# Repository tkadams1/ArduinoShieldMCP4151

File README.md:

# ArduinoShieldMCP4151
Code for driving the Arduino shield including a python serial monitor program, ROS2 subscriber code, and the necessary code to Drive the arduino.  Also include is the custom arduino shield KiCad files to create the shield itself.

Component List:
  - MCP 4151 digital potentiometer
  - JZC-11F relay
  - 5k ohms THT resistor
  - Arduino header pins
  - 2.54 mm 2 socket screw terminals

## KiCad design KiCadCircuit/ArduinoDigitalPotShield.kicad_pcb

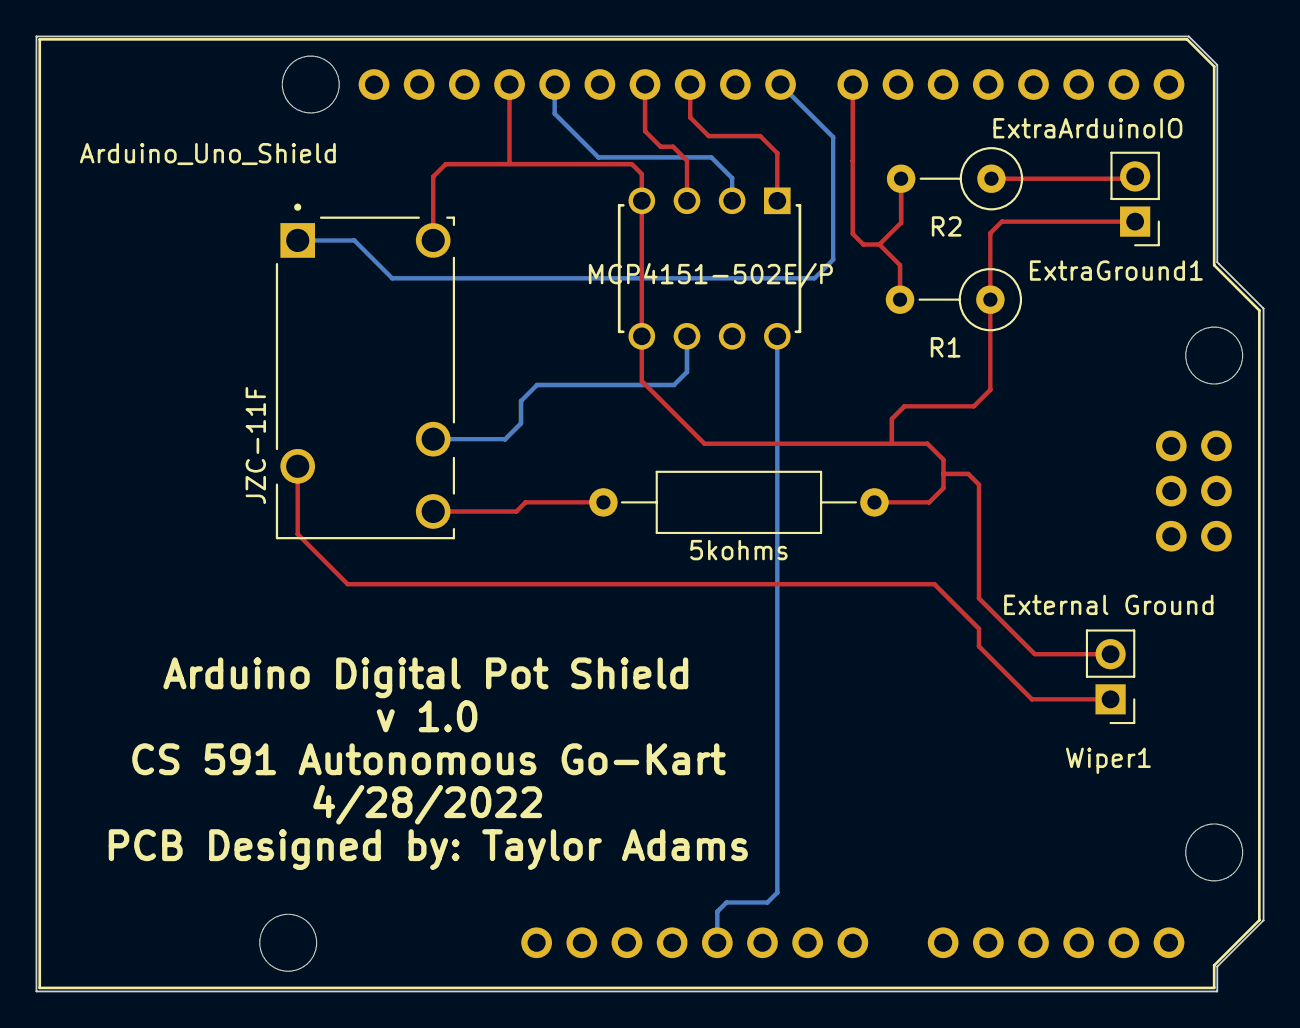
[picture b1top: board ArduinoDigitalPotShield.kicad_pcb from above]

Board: 2 copper layers, 69.0 x 53.7 mm, 8 parts (0 on the bottom side), 11 nets.

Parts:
5kohms: R; R_Axial_DIN0309_L9.0mm_D3.2mm_P15.24mm_Horizontal
ExtraGround1: ExtraArduinoIO; PinHeader_1x02_P2.54mm_Vertical
K1: JZC-11F; RELAY_J0971CS5VDC.45
R1, R2: R; R_Axial_DIN0309_L9.0mm_D3.2mm_P5.08mm_Vertical
U2: MCP4151-502E/P; DIP254P762X533-8
Wiper1: External Ground; PinHeader_1x02_P2.54mm_Vertical
XA1: Arduino_Uno_Shield

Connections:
unnamed: 5kohms.1, ExtraGround1.1, K1.A2, R1.1, U2.4 (VSS), U2.5 (P0A), Wiper1.2, XA1.GND1 (GND)
unnamed: 5kohms.2, K1.14
unnamed: ExtraGround1.2, R2.1
unnamed: K1.11, Wiper1.1
unnamed: K1.12, U2.6 (P0W)
unnamed: K1.A1, XA1.D8
unnamed: R1.2, R2.2, XA1.D7
unnamed: U2.1 (~CS), XA1.D10 (D10_CS)
unnamed: U2.2 (SCK), XA1.D13
unnamed: U2.3 (SDI/SDO), XA1.D11
unnamed: U2.8 (VDD), XA1.5V1 (5V)

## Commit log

2022-06-01 Initial Commit containing completed circuit and code
2022-06-03 Fixed readme bullet points
